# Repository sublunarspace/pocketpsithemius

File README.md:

# Pocket Psithemius

The Psithemius is a psionic device for spirit conjuration and magical manifestation.

Its basic architecture consists of printed circuit boards hosting concentric circles with magical names and symbols and a triangle with a spiral shaped transmitter in its center. The design is based on a system attributed to the German abbot and polymath Johannes Trithemius who lived around the end of the 15th century and developed methods for communing with transdimensional entities.

For the Psithemius device to work properly, a quartz crystal is needed. The device emits light and an electromagnetic field around and into this quartz crystal set in the center of the triangle that acts as a focal point and spirit medium.

The Psithemius device utilizes principles from Psionics to detect and electrically amplify intent in the form of magical sigils or radionic rates sent to it. The goal is to charge the crystal with energies resonating with the nature of an entity and act as a beacon of condensed intent to attract them to the ritual space.

## Get the Psithemius

You can [purchase a Pocket Psithemius directly from Sublunar Psionics](mailto:info@sublunar.space). It comes in three different versions. All versions come with a USB power cable and a small carry bag.

* Fully assembled device (EUR 99.00)
* DIY kit incl. PCBs and all components (EUR 69.00)
* PCBs only - without components (EUR 49.00)

[Operator Manual](MANUAL.md)

[Assembly Instructions](hardware/ASSEMBLY.md)

[BOM List of Components](hardware/BOM.csv) / [PDF](hardware/BOM.pdf)

[Component Images](hardware/parts_preview.pdf)

## Code the Psithemius

Modify the firmware that runs the Psithemius or write your own from scratch. It's all fully Arduino compatible.

[Arduino IDE Firmware](firmware/)

## Fork the Psithemius

You can download the KiCAD project files (schematic, circuit board design, gerber files) and manufacture your own Psithemius or modify it

[KiCAD Files](hardware/)

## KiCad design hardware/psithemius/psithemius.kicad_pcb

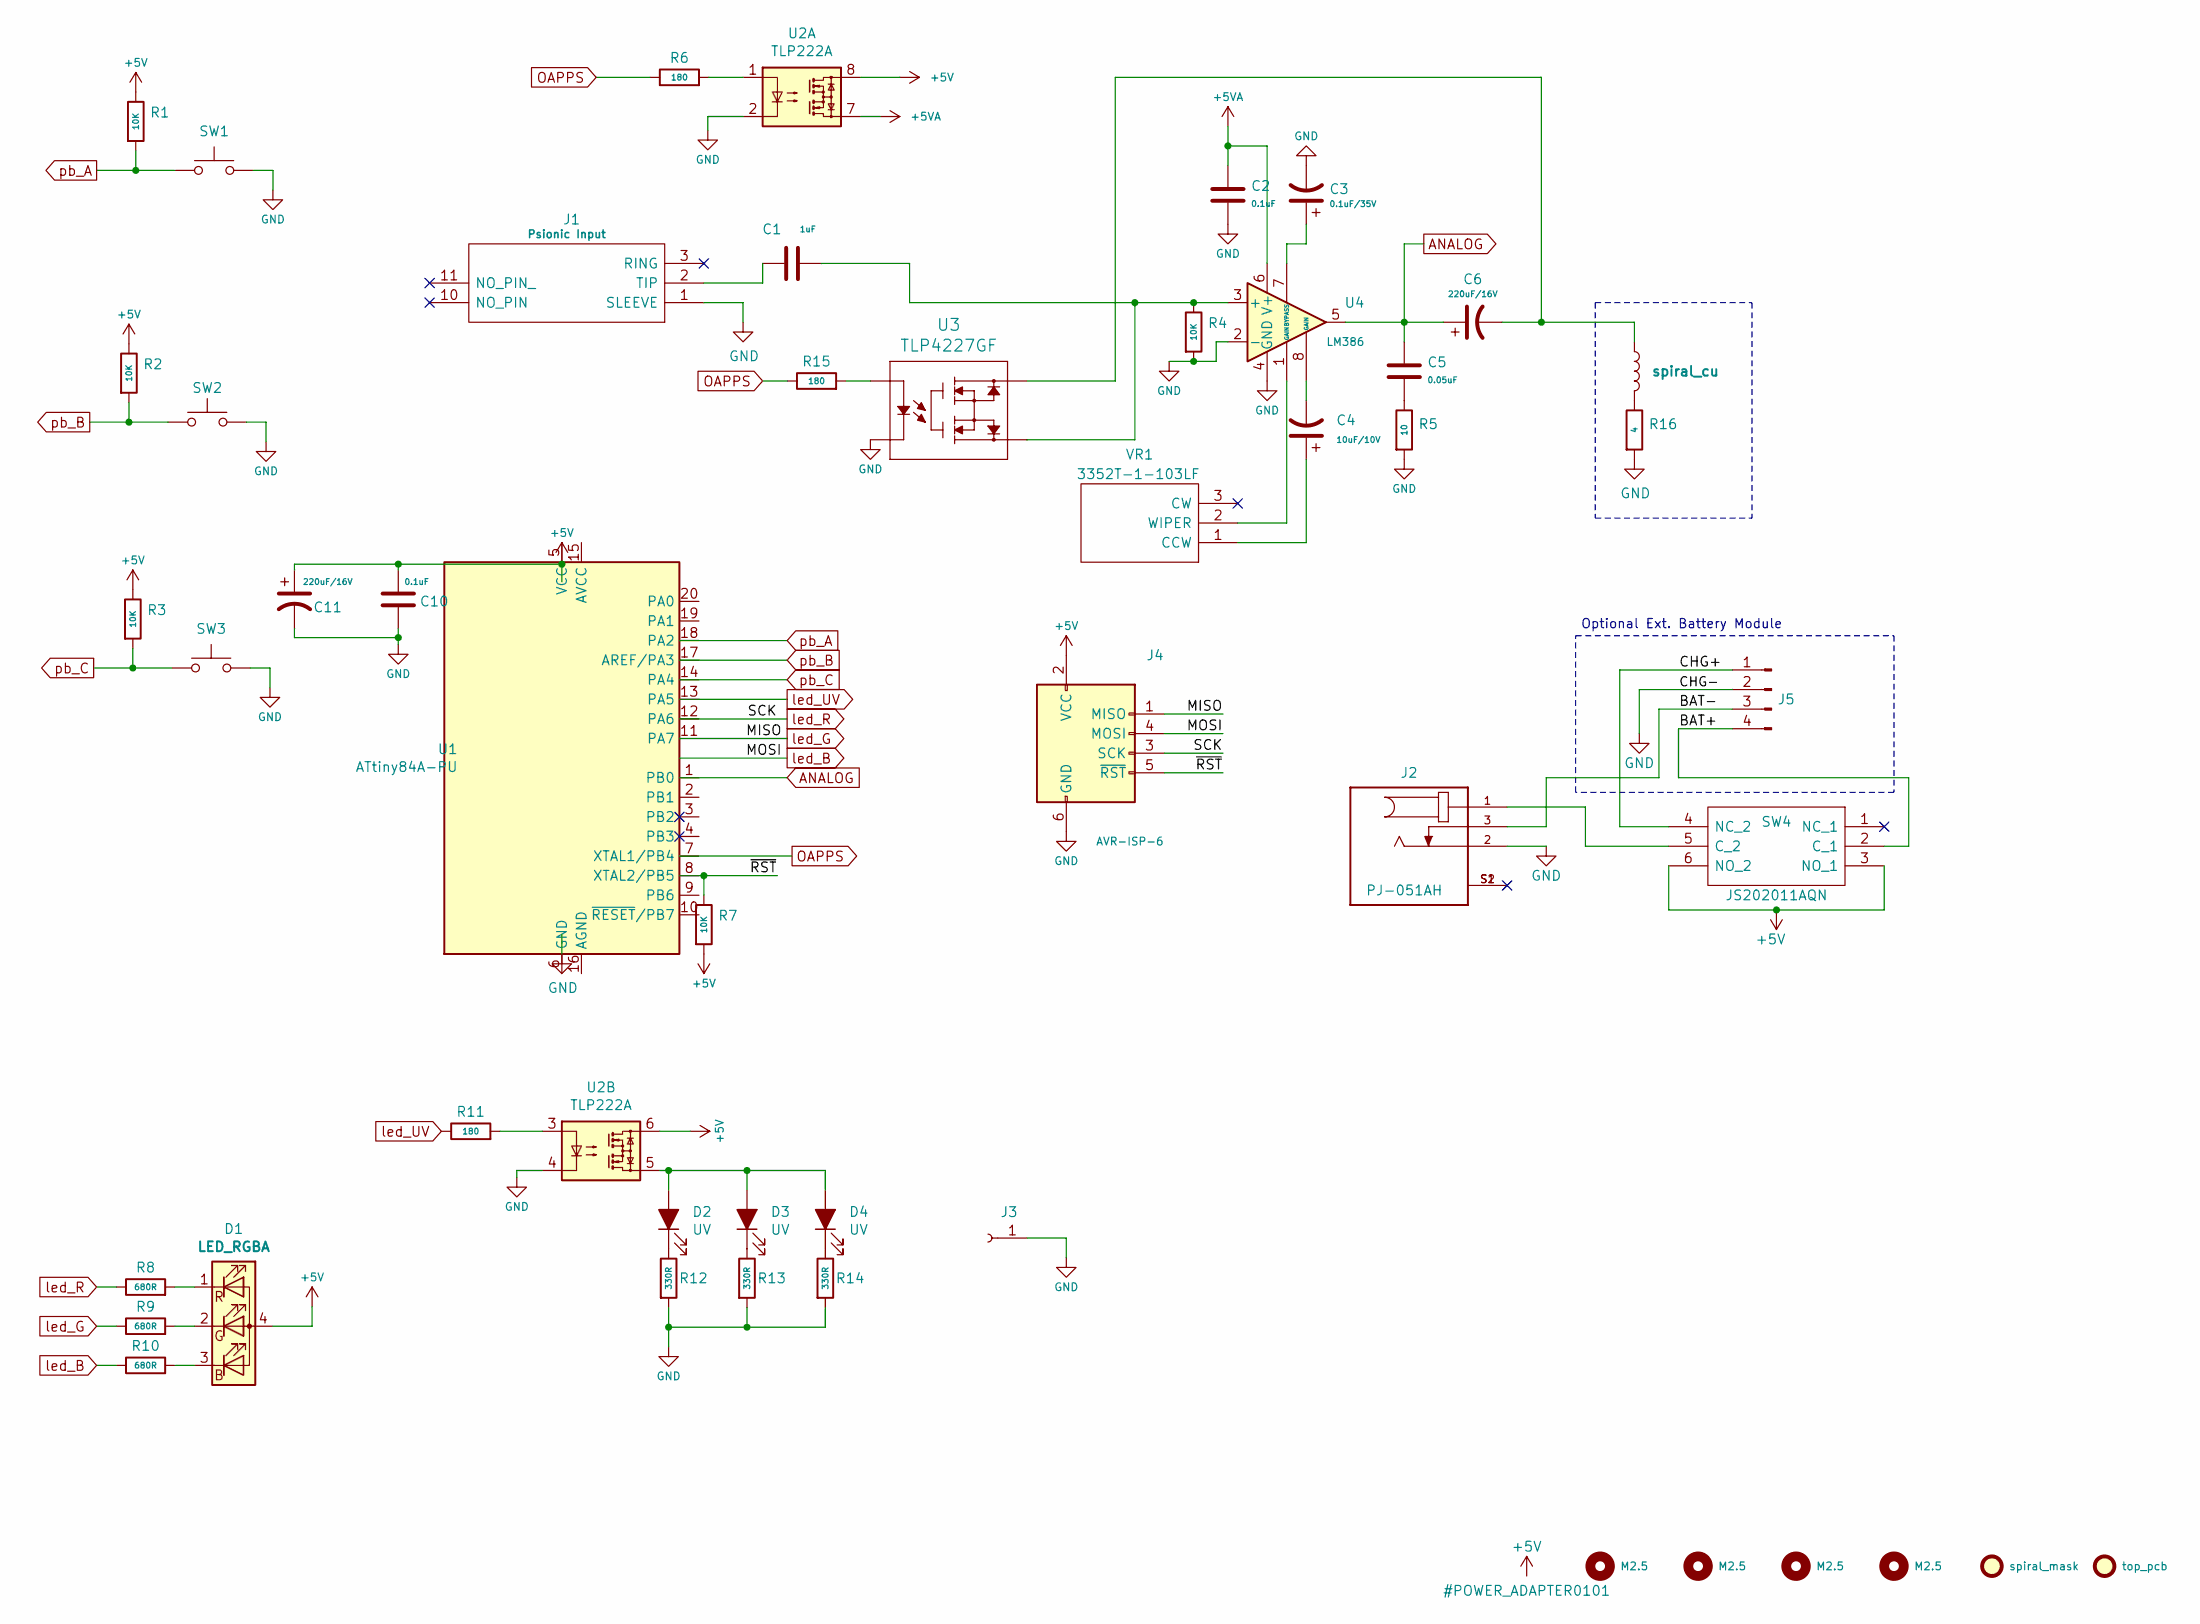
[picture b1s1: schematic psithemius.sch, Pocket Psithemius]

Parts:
C1: 1uF; C_Disc_D5.1mm_W3.2mm_P5.00mm; Part Number K105Z20Y5VF5TH5; Digi-Key BC1168CT-ND
C2, C10: 0.1uF; C_Disc_D4.7mm_W2.5mm_P5.00mm; Part Number K104K15X7RF5TH5; Digi-Key BC1101CT-ND
C3: 0.1uF/35V; CP_Radial_D4.0mm_P1.50mm; Part Number UMA1H0R1MCD2TP; Digi-Key 493-10420-3-ND
C4: 10uF/10V; CP_Radial_D4.0mm_P1.50mm; Part Number USV1C100MFD; Digi-Key 493-16020-ND
C5: 0.05uF; C_Disc_D4.7mm_W2.5mm_P5.00mm; Part Number 89350; Digi-Key 2368-89350-ND
C6, C11: 220uF/16V; CP_Radial_D8.0mm_P5.00mm; Part Number USR1C221MDD; Digi-Key 493-15996-ND
D1: LED_RGBA; WurthElektronik_156125M173000; Part Number 156125M173000; Digi-Key 732-11426-1-ND
D2, D3, D4: UV; LED_D5.0mm_Clear; Part Number VAOL-5GUV8T4; Digi-Key VAOL-5GUV8T4-ND
FID1: spiral_mask; LOGOТ_MASK; Part Number - - -; Digi-Key - - -
FID2: top_pcb; trithemius_top; Part Number - - -; Digi-Key - - -
FID3: spiral_cu; LOGO1; Part Number - - -; Digi-Key - - -
H1, H2, H3, H4: M2.5; RAF_M1257-2545-AL
J1: Psionic Input; SJ13523N; Part Number SJ1-3523N; Digi-Key CP1-3523N-ND
J2: PJ-051AH; CUI_PJ-051AH; Part Number PJ-051AH; Digi-Key CP-051AH-ND
J3: 7761; Earth; Part Number 7761; Digi-Key 36-7761-ND
J4: AVR-ISP-6; IDC-Header_2x03_P2.54mm_Horizontal; Part Number 61200621721; Digi-Key 732-5404-ND
J5: Internal Power; JST_PH_S4B-PH-K_1x04_P2.00mm_Horizontal; Part Number S4B-PH-K-S(LF)(SN); Digi-Key 455-1721-ND
R1, R2, R3, R4, R7: 10K; R_Axial_DIN0204_L3.6mm_D1.6mm_P7.62mm_Horizontal; Part Number CF18JT10K0; Digi-Key CF18JT10K0CT-ND
R5: 10; R_Axial_DIN0204_L3.6mm_D1.6mm_P7.62mm_Horizontal; Part Number CF18JT10R0; Digi-Key CF18JT10R0CT-ND
R6, R11, R15: 180; R_Axial_DIN0204_L3.6mm_D1.6mm_P7.62mm_Horizontal; Part Number CF18JT180R; Digi-Key CF18JT180RCT-ND
R8, R9, R10: 680R; R_Axial_DIN0204_L3.6mm_D1.6mm_P7.62mm_Horizontal; Part Number CF18JT680R; Digi-Key CF18JT680RCT-ND
R12, R13, R14: 330R; R_Axial_DIN0204_L3.6mm_D1.6mm_P7.62mm_Horizontal; Part Number CF18JT330R; Digi-Key CF18JT330RCT-ND
R16: 4; R_Axial_DIN0614_L14.3mm_D5.7mm_P20.32mm_Horizontal; Part Number WW1AFT4R00; Digi-Key WW1AFT4R00-ND
SW1, SW2, SW3: B3F-4050; SW_Tactile_SPST-NO_Omron_B3F-40xx; Part Number B3F-4050; Digi-Key SW413-ND
SW4: JS202011AQN; Mouser Part Number 611-JS202011AQN
U1: ATtiny84A-PU; DIP-14_W7.62mm; Part Number ATTINY84-20PU; Digi-Key ATTINY84-20PU-ND
U2: TLP222A; DIP-8_W7.62mm; Part Number TLP222A-2(F); Digi-Key TLP222A-2F-ND
U3: TLP4227GF; DIP-4_W7.62mm; Part Number TLP4227GF; Digi-Key TLP4227GF-ND
U4: LM386; DIP-8_W7.62mm; Part Number LM386MX-1/NOPB; Digi-Key 296-44414-5-ND
VR1: 3352T-1-103LF; 3352T1103LF; Mouser Part Number 652-3352T-1-103LF

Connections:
+5V: C10.2, C11.1, D1.4 (A), J4.2 (VCC), R1.1, R2.1, R3.1, R7.2, SW4.3 (NO_1), SW4.6 (NO_2), U2.6, U2.8
+5VA: C2.1, U2.7, U4.6 (V+)
/BAT+: J5.4, SW4.2 (C_1)
/BAT-: J2.3, J5.3
/CHG+: J5.1, SW4.4 (NC_2)
/~RST: J4.5 (~RST), R7.1
ANALOG: C5.1, C6.1, U4.5
GND: C2.2, C3.2, C10.1, C11.2, J1.1 (SLEEVE), J2.2, J3.1, J4.6 (GND), J5.2, R4.2, R5.2, R12.2, R13.2, R14.2, R16.2, SW1.2, SW2.2, SW3.2, U2.2, U2.4, U3.2, U4.2 (-), U4.4 (GND)
unnamed: C1.1, R4.1, U3.3 (DRAIN), U4.3 (+)
unnamed: C1.2, J1.2 (TIP)
unnamed: C3.1, U4.7 (BYPASS)
unnamed: C4.1, VR1.1 (CCW)
unnamed: C4.2, U4.8 (GAIN)
unnamed: C5.2, R5.1
unnamed: C6.2, FID3.1, U3.4 (DRAIN)
unnamed: D1.1 (RK), R8.2
unnamed: D1.2 (GK), R9.2
unnamed: D1.3 (BK), R10.2
unnamed: D2.1 (K), R12.1
unnamed: D2.2 (A), D3.2 (A), D4.2 (A), U2.5
unnamed: D3.1 (K), R13.1
unnamed: D4.1 (K), R14.1
unnamed: FID3.2, R16.1
unnamed: J2.1, SW4.5 (C_2)
unnamed: J2.S1 (SHIELD), J2.S2 (SHIELD)
unnamed: R6.2, U2.1
unnamed: R11.2, U2.3
unnamed: R15.2, U3.1
unnamed: U4.1 (GAIN), VR1.2 (WIPER)
OAPPS: R6.1, R15.1
led_B: J4.4 (MOSI), R10.1
led_G: J4.1 (MISO), R9.1
led_R: J4.3 (SCK), R8.1
led_UV: R11.1
pb_A: R1.2, SW1.1
pb_B: R2.2, SW2.1
pb_C: R3.2, SW3.1

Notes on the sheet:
Optional Ext. Battery Module

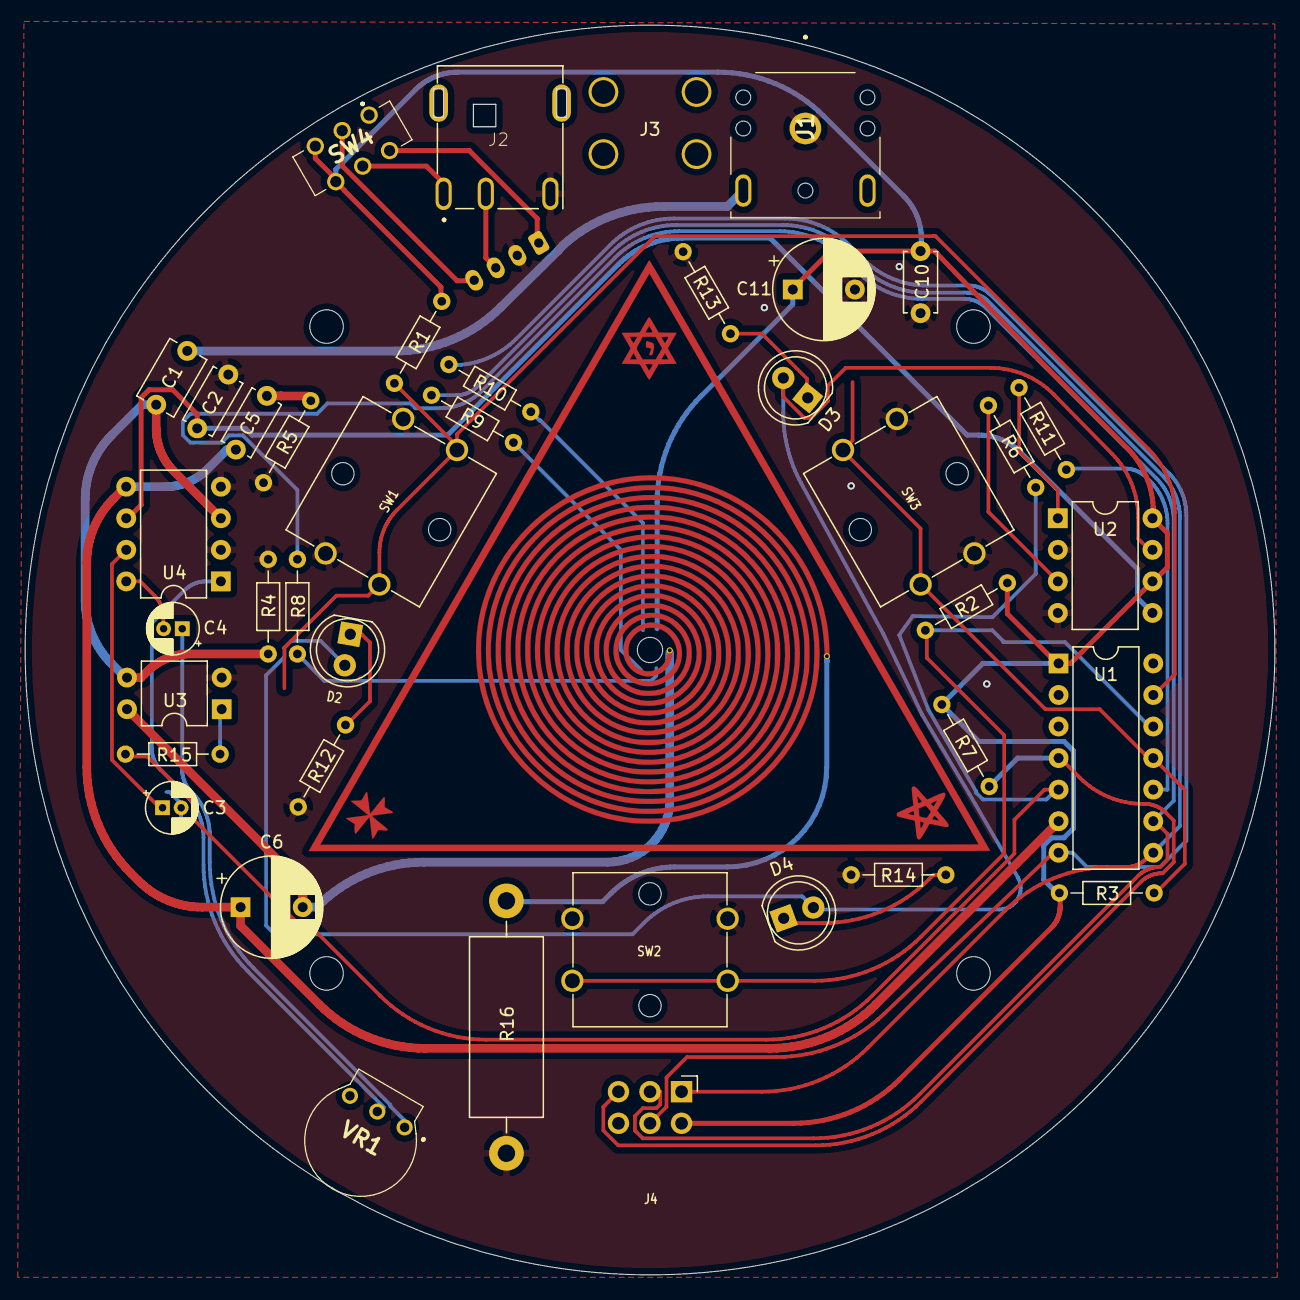
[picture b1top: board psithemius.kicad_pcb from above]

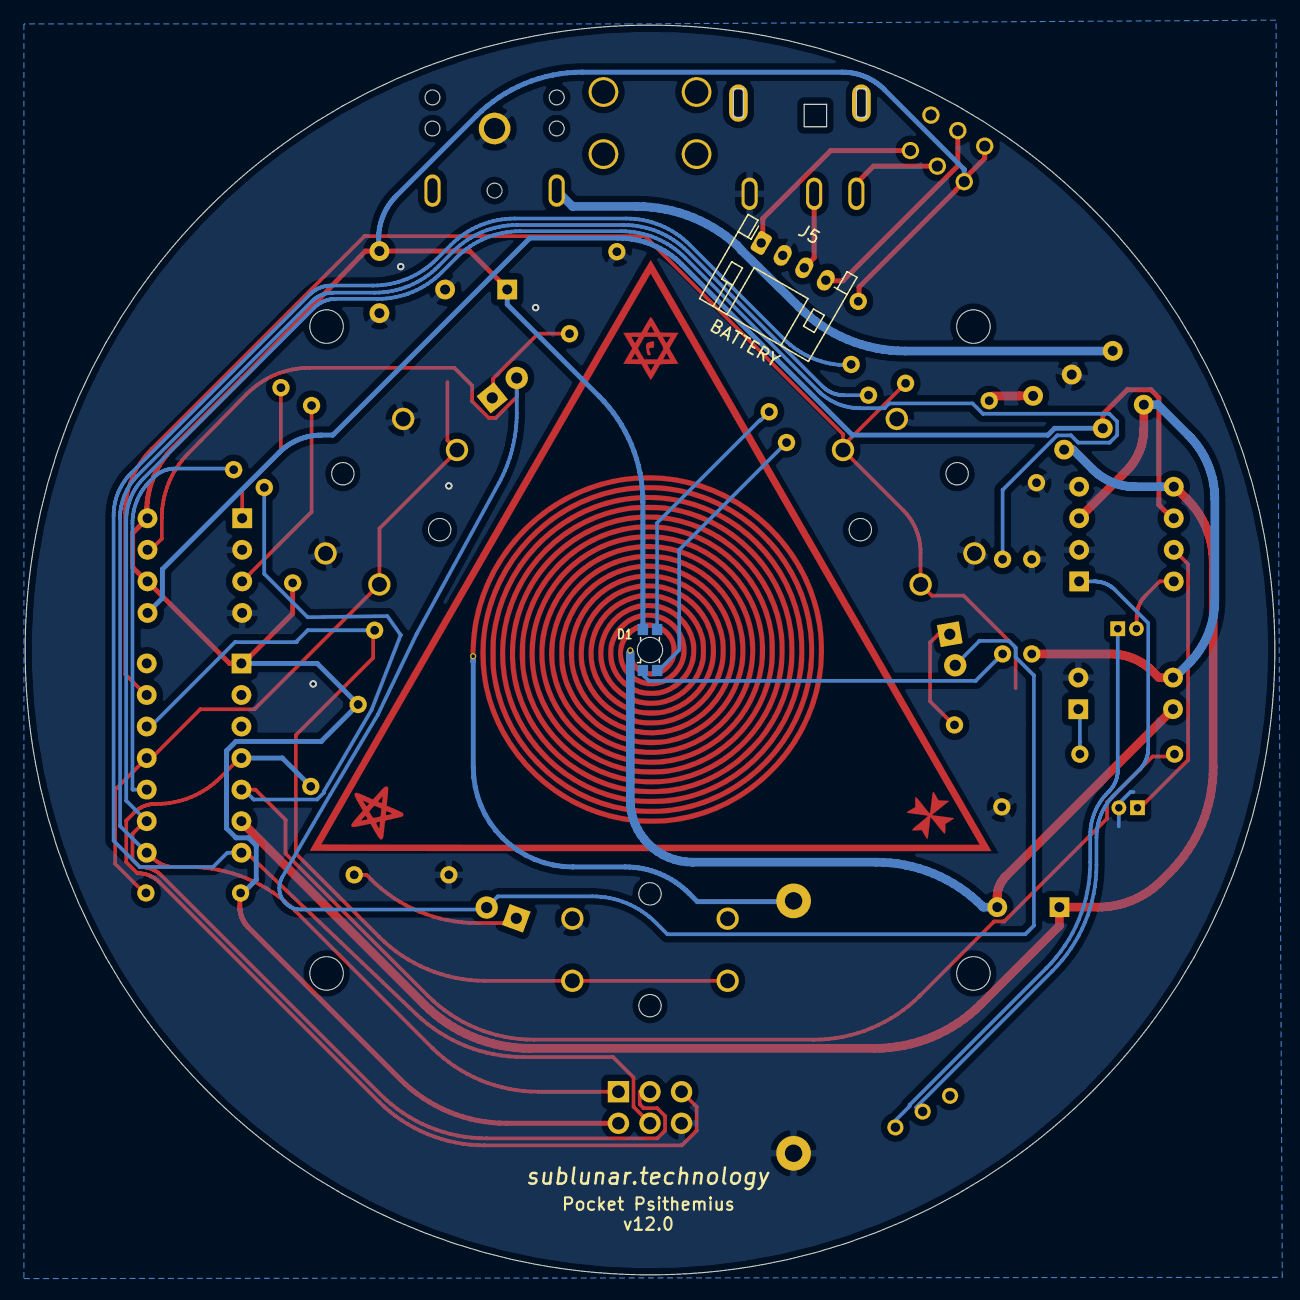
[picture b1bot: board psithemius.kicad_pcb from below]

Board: 2 copper layers, 100.6 x 100.6 mm, 49 parts (2 on the bottom side), 36 nets.

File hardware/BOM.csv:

Reference,Quantity,Value,Description,Datasheet,Manufacturer,Part Number,Digikey Number,Mouser Number
,,,,,,,,
C1,1,1uF,Capacitor,http://www.vishay.com/docs/45171/kseries.pdf,Vishay,K105Z20Y5VF5TH5,BC1168CT-ND,594-K105Z20Y5VF5TH5
"C2, C5, C10",2,0.1uF,Capacitor,http://www.vishay.com/docs/45171/kseries.pdf,Vishay,K104K15X7RF5TH5,BC1101CT-ND,594-K104K15X7RF5TH5
C3,1,0.1uF/35V,Pol. Capacitor,https://www.nichicon.co.jp/english/products/pdfs/e-uma.pdf,Nishicon,UMA1H0R1MCD2TP,493-10420-3-ND,N/A
C4,1,10uF/10V,Pol. Capacitor,http://nichicon-us.com/english/products/pdfs/e-usv.pdf,Vishay,USV1C100MFD,493-16020-ND,647-USV1C100MFD1TE647-USV1C100MFD1TE
"C6, C11",2,220uF/16V,Pol. Capacitor,http://nichicon-us.com/english/products/pdfs/e-usa_usr.pdf,Nishicon,USR1C221MDD,493-15996-ND,647-USR1C221MDD
D1,1,LED_RGBA,RGB LED,https://katalog.we-online.de/led/datasheet/156125M173000.pdf,Würth Elektronik,156125M173000,732-11426-1-ND,710-156125M173000
"D2, D3, D4",3,UV,UV LED,http://static.vcclite.com/pdf/VAOL-5GUV8T4-LED-5mm-UV.pdf,Nichia,VAOL-5GUV8T4,VAOL-5GUV8T4-ND,593-VAOL5GUV8T4
"H1, H2, H3, H4",4,M2.5/9mm,Distance Bolt,https://katalog.we-online.de/em/datasheet/960xxxxxx.pdf,Würth Elektronik,960090021,732-12693-ND,N/A
"H1, H2, H3, H4",4,M2.5/7mm,Distance Bolt,https://katalog.we-online.de/em/datasheet/960xxxxxx.pdf,Würth Elektronik,960070021,732-12683-ND,N/A
"H1, H2, H3, H4",4,M2.5/25mm,Screw,N/A,N/A,10.9-7380-M2.5x20,N/A,N/A
"H1, H2, H3, H4",4,M2.5,Washer,N/A,N/A,ST-M2.5-125,N/A,N/A
"H1, H2, H3, H4",4,M2.5,Nut,N/A,N/A,ST-M2.5-934,N/A,N/A
J1,1,3.5mm,Audio Mini Jack,https://www.cuidevices.com/product/resource/digikeypdf/sj1-3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,CUI Devices,SJ1-3523N,CP1-3523N-ND,490-SJ1-3523N
J2,1,PJ-051AH,Barrel Jack,https://www.cuidevices.com/product/resource/pj-051ah.pdf,CUI Devices,PJ-051AH,CP-051AH-ND,490-PJ-051AH
J3,1,7761,M2.5 / Earth,http://keyelco.com/userAssets/file/M65p69.pdf,Keystone Electronics,7761,36-7761-ND,534-7761
J4,1,AVR-ISP-6,Flat Cable Socket,https://katalog.we-online.de/em/datasheet/6120xx21721.pdf,Würth Elektronik,61200621721,732-5404-ND,710-61200621721
J5,1,BAT,Battery Socket,http://www.jst-mfg.com/product/pdf/eng/ePH.pdf,JST,S4B-PH-K-S(LF)(SN),455-1721-ND,N/A
"R1, R2, R3, R4, R7",5,10K,Resistor,https://www.seielect.com/catalog/sei-cf_cfm.pdf,Stackpole Electronics,CF18JT10K0,CF18JT10K0CT-ND,N/A
R5,1,10,Resistor,https://www.seielect.com/catalog/sei-cf_cfm.pdf,Stackpole Electronics,CF18JT10R0,CF18JT10R0CT-ND,N/A
"R6, R11, R15",3,180,Resistor,https://www.seielect.com/catalog/sei-cf_cfm.pdf,Stackpole Electronics,CF18JT180R,CF18JT180RCT-ND,N/A
"R8, R9, R10",3,680,Resistor,https://www.seielect.com/catalog/sei-cf_cfm.pdf,Stackpole Electronics,CF18JT680R,CF18JT680RCT-ND,N/A
"R12, R13, R14",3,330,Resistor,https://www.seielect.com/catalog/sei-cf_cfm.pdf,Stackpole Electronics,CF18JT330R,CF18JT330RCT-ND,N/A
R16,1,4,Resistor,https://www.seielect.com/catalog/sei-cf_cfm.pdf,Stackpole Electronics,WW1AFT4R00,WW1AFT4R00-ND,N/A
"SW1, SW2, SW3",3,B3F-4050,Switch,https://omronfs.omron.com/en_US/ecb/products/pdf/en-b3f.pdf,Omron,B3F-4050,SW413-ND,653-B3F-4050
"SW1, SW2, SW3",3,,Switch Cap,https://omronfs.omron.com/en_US/ecb/products/pdf/en-b32.pdf,Omron,B32-1610 ,SW847-ND,653-B32-1610
SW4,1,JS202011AQN,Switch,https://www.ckswitches.com/media/1422/js.pdf,C & K,JS202011AQN,401-2000-ND,611-JS202011AQN
U1,1,ATtiny84A-PU,Microcontroller,http://ww1.microchip.com/downloads/en/DeviceDoc/doc8183.pdf,Microchip Technology,ATTINY84-20PU,ATTINY84-20PU-ND,556-ATTINY84-20PU
U2,1,TLP222A,Optical Relay,https://toshiba.semicon-storage.com/info/docget.jsp?did=1703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,Toshiba,TLP222A-2(F),TLP222A-2F-ND,757-TLP222A-2(F)
U3,1,TLP4227GF,Optical Relay,http://toshiba.semicon-storage.com/info/docget.jsp?did=17079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,Toshiba,TLP4227GF,TLP4227GF-ND,757-TLP4227G(F)
U4,1,LM386,Op-Amp,http://www.ti.com/lit/ds/symlink/lm386.pdf,Texas Instruments,LM386MX-1/NOPB,296-44414-5-ND,926-LM386MX-1/NOPB
VR1,1,3352T-1-103LF,Var. Resistor,https://www.bourns.com/docs/Product-Datasheets/3352.pdf,Bourns,3352T-1-103LF,3352T-103LF-ND,652-3352T-1-103LF

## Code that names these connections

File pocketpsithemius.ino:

/*Copyright (c) 2020 Sublunar Psionics

Special Thanks to Slavko Andrejevic for providing the main framework of this
firmware and for technical support.

---- MIT License ----

Permission is hereby granted, free of charge, to any person obtaining a copy
of this software and associated documentation files (the "Software"), to deal
in the Software without restriction, including without limitation the rights
to use, copy, modify, merge, publish, distribute, sublicense, and/or sell
copies of the Software, and to permit persons to whom the Software is
furnished to do so, subject to the following conditions:

The above copyright notice and this permission notice shall be included in all
copies or substantial portions of the Software.

THE SOFTWARE IS PROVIDED "AS IS", WITHOUT WARRANTY OF ANY KIND, EXPRESS OR
IMPLIED, INCLUDING BUT NOT LIMITED TO THE WARRANTIES OF MERCHANTABILITY,
FITNESS FOR A PARTICULAR PURPOSE AND NONINFRINGEMENT. IN NO EVENT SHALL THE
AUTHORS OR COPYRIGHT HOLDERS BE LIABLE FOR ANY CLAIM, DAMAGES OR OTHER
LIABILITY, WHETHER IN AN ACTION OF CONTRACT, TORT OR OTHERWISE, ARISING FROM,
OUT OF OR IN CONNECTION WITH THE SOFTWARE OR THE USE OR OTHER DEALINGS IN THE
SOFTWARE.

*/

#include <OneButton.h>

#define btnA            0      // PA0 / Button A:
#define btnB            2      // PA1 / Button B:
#define btnC            1      // PA2 / Button C:
#define led_R           4      // PA4 / RED LED
#define led_G           5      // PA5 / GREEN LED
#define led_B           6      // PA6 / BLUE LED
#define uv_LED          3      // PA3 / UV LED
#define OPAMP           8      // PB2 / turns on the Op Amp circuit
#define ANALOG          7      // PA7 / Get analog
#define REG1            9      // PB1 / unconnected
#define REG2           10      // PB0 / unconnected

#define ON              HIGH
#define OFF             LOW

//---- BUTTONS ----

byte counterA         = 0;     // count push btnA:
byte counterB         = 0;     // count push btnB:
byte counterC         = 0;     // count push btnC:
bool enabled_btnAC    = true;  // Button A + C enabled or not
bool enabled_btnB     = true;  // Button B enabled or not

OneButton buttonA(btnA, true); // Button A setup
OneButton buttonB(btnB, true); // Button B setup
OneButton buttonC(btnC, true); // Button C setup

//---- LEDS ----

bool enabled_LED      = false; //turn on a tricolor LED
bool usePWM           = false; //use softPWM for more nuanced colors
bool disco            = false; // random colors

//---- TIMER ----

bool countDelay       = false; //are we counting ticks to time out the UV LEDs?
uint32_t oldTime      = millis();

//---- COLOR ----

struct COLOR { // Creating structure for colors
  byte r;
  byte g;
  byte b;
};
COLOR selectedColor   = { 0, 0, 0 };

//---- PLANETARY COLORS ----

COLOR white           = { 255 , 255 , 255 }; // Moon correspondence
COLOR orange          = { 255 , 128 ,   0 }; // Mercury correspondence
COLOR green           = {   0 , 255 ,   0 }; // Venus correspondence
COLOR yellow          = { 255 , 255 ,   0 }; // Sol correspondence
COLOR red             = { 255 ,   0 ,   0 }; // Mars correspondence
COLOR blue            = {   0 , 128 , 255 }; // Jupiter correspondence
COLOR purple          = { 128 ,   0 , 128 }; // Jupiter/Moon correspondence
COLOR indigo          = { 111 ,   0 , 255 }; // Saturn correspondence
COLOR grey            = {  40 ,  40 ,  40 }; // Saturn correspondence

//---- DEVICE SETUP ----
void setup() {

  // BUTTONS
  buttonA.attachClick(cycleColors);
  buttonA.attachLongPressStart(discoStart);
  buttonB.attachClick(ultraviolet);
  buttonB.attachLongPressStart(uvForever);
  buttonC.attachClick(opAmp);

  // LEDS
  pinMode(led_B, OUTPUT);
  pinMode(led_G, OUTPUT);
  pinMode(led_R, OUTPUT);
  offLeds();

  // UV LED
  pinMode(uv_LED, OUTPUT);
  digitalWrite(uv_LED, OFF);

  // OP AMP
  //pinMode(ANALOG, INPUT);
  pinMode(OPAMP, OUTPUT);
  digitalWrite(OPAMP, OFF);

}

//---- DEVICE LOOP ----
void loop() {

  buttonA.tick();
  buttonB.tick();
  buttonC.tick();
  showColor();

  // If enabled, turns UV LED off after 1min
  if ( countDelay == true && ((millis()-oldTime) > 60000)) {
    //Turn the UV LED off
    enabled_btnAC = true;
    digitalWrite(uv_LED, OFF);
    counterB = 0;
    countDelay = false;
  }

  if ( disco == true ) {
    enabled_LED = true;
    usePWM = false;
    selectedColor.r = rng();
    selectedColor.g = rng();
    selectedColor.b = rng();
    //digitalWrite(uv_LED, bitRead(rng(), 0));
    showColor();
    delay(rng());
  }
  
}

//---- FUNCTIONS ----

// turn all LEDs off
void offLeds() {
  analogWrite(led_R, 255);
  analogWrite(led_B, 255);
  analogWrite(led_G, 255);
}

// set a color
void setColor(COLOR paint, bool full = true) {
  //tricolor LED color
  selectedColor.r = paint.r;
  selectedColor.b = paint.b;
  selectedColor.g = paint.g;
  showColor();
}

// show the color or turn off
void showColor() { // 100% of color
  if (enabled_LED == true) {
      softPWM(led_R, selectedColor.r, 1);
      softPWM(led_B, selectedColor.b, 1);
      softPWM(led_G, selectedColor.g, 1);
  } else {
    offLeds();
  }
}

void discoStart() {
  if ( disco == true ) {
    disco = false;
    enabled_LED = false;
    //digitalWrite(uv_LED, OFF);
    counterA = 0;
  }
  else disco = true;
}

// used for button A to cycle through the colors
void cycleColors() {
  if ( disco == true) discoStart();
  if (enabled_btnAC == true) {
    counterA++;
    switch (counterA) {
      case 1:
        enabled_LED = true;
        setColor(white, true);
        break;
      case 2:
        usePWM = true;
        setColor(orange, true);
        break;
      case 3:
        usePWM = false;
        setColor(green, true);
        break;
      case 4:
        setColor(yellow, true);
        break;
      case 5:
        setColor(red, true);
        break;
      case 6:
        setColor(blue, true);
        break;
      case 7:
        usePWM = true;
        setColor(purple, true);
        break;
      case 8:
        setColor(indigo, true);
        break;
      case 9:
        setColor(grey, true);
        break;
      case 10:
        enabled_LED = false;
        counterA = 0;//TURN OFF
        break;
    }
  }
}

// used for button B to toggle the UV LEDs
void ultraviolet() {
  counterA = 0;
  if ( disco == true) discoStart();
  if (enabled_btnB == true) {
    counterB++;
    switch (counterB) {
      case 1:
        blinker(led_B, 500, 5);
        enabled_LED = false;
        enabled_btnAC = false;
        digitalWrite(uv_LED, ON);
        if ( countDelay == false ) {
          oldTime    = millis();
        }
        countDelay = true; // turn on delay counter in loop()
        break;
      case 2:
        enabled_btnAC = true;
        digitalWrite(uv_LED, OFF);
        counterB = 0;
        break;
    }
  }
}

// disable all buttons and keep UV light running forever
void uvForever() {
  blinker(led_B, 500, 5);
  blinker(led_B, 50, 10);
  enabled_btnB = false;
  enabled_btnAC = false;
  countDelay = false;
  digitalWrite(uv_LED, ON);
}

// used for button C to toggle the OP Amp
void opAmp() {
  if (enabled_btnAC == true) {
    counterC++;
    switch (counterC) {
      case 1:
        blinker(led_G, 50, 2);
        digitalWrite(OPAMP, ON);
        break;
      case 2:
        blinker(led_R, 50, 2);
        digitalWrite(OPAMP, OFF);
        counterC = 0;
        break;
    }
  }
}

// helper to blink a color
void blinker(byte pin, int len, byte rep) {
  byte counter = 1;
  while (counter <= rep) {
    analogWrite(pin, 0);
    delay(len);
    offLeds();
    delay(len);
    counter++;
  }
}

// software PWM function that fakes analog output
void softPWM(byte pin, byte freq, byte sp) {
  byte delay1 = 255 - freq;
  if (usePWM == true) {
    while (sp > 0) {
      digitalWrite(pin, LOW); //on
      delayMicroseconds(freq);
      digitalWrite(pin, HIGH); //off
      delayMicroseconds(delay1);
      sp--;
    }
  } else {
    analogWrite(pin, 255 - freq);
  }
}

byte rng() {
  int raw0, raw1;
  byte b0, b1, x, col, twoBytes[2], result;
  col = 0;
  while ( col <= 1 ) {
    raw0 = analogRead(REG1);
    raw1 = analogRead(REG2);
    b0 = lowByte(raw0);
    b1 = lowByte(raw1);
    x = b0 ^ b1;
    twoBytes[col] = x;
    col++;
  }
  result = (twoBytes[0]<<4)+twoBytes[1];
  return result;
}

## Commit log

2020-04-19 init
2020-04-24 credits
2020-04-24 added Attiny84 extra functionality
2020-04-24 declare and setup ANALOG
2020-04-24 removed binaries
2020-04-24 fixed indents
2020-06-03 changed functionality for Attiny84
2020-06-03 fixed
2020-06-17 added random colors
2020-06-18 added KiCAD Files and MANUAL.md
2020-06-18 added image + links
2020-06-18 fixed link
2020-06-18 added cardinal direction info
2020-06-18 fixed wording
2020-06-18 added link
2020-06-18 improved wording
2020-06-18 typos
2020-06-18 removed .bak
2020-06-21 added BOM.csv
2020-06-21 added ASSEMBLY instructions
2020-06-21 added pdfs and jpgs
2020-06-21 added contact
2020-06-21 typo
2020-06-24 folder fix
2020-06-29 SW4 is S1
2020-07-13 changed assembly order
